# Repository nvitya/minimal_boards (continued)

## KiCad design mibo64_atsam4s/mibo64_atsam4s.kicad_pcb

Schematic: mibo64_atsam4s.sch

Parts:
C1: 10nF; C_0603_HandSoldering
C2, C3: 22pF; C_0603_HandSoldering
C4, C5, C7, C8, C9, C13, C14: 100nF; C_0603_HandSoldering
C6, C12: 10uF; C_0603_HandSoldering
C10, C11: 1uF; C_0603_HandSoldering
D1: YELLOW; LED_0603_HandSoldering
D2: GREEN; LED_0603_HandSoldering
J1: EXT1; Pin_Header_Straight_1x26_Pitch2.54mm
J2: SWD; Pin_Header_Straight_1x04_Pitch2.54mm
J3: EXT2; Pin_Header_Straight_1x26_Pitch2.54mm
J4: USB_OTG; USB_Micro-B
MK1, MK2: Mounting_Hole; MountingHole_3.2mm_M3
R1: 10k; R_0603_HandSoldering
R2, R3: 1k; R_0603_HandSoldering
R4, R5: 22R; R_0603_HandSoldering
SW1: RESET; SW_SPST_FSMSM
U1: ATSAM4SxB; LQFP-64_10x10mm_Pitch0.5mm
U2: LD1117S33CTR; SOT-223
Y1: 12MHz; Crystal_HC49-4H_Vertical

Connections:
+3V3: C4.1, C5.1, C7.1, C9.1, C10.1, C12.1, D1.2, D2.2, J1.2, J2.1, J3.25, R1.2, U1.1 (ADVREF), U1.7 (VDDIN), U1.18 (VDDIO), U1.45 (VDDIO), U1.58 (VDDIO), U2.2 (VO)
/1V2: C11.1, C13.1, C14.1, U1.8 (VDDOUT), U1.12 (VDDCORE), U1.24 (VDDCORE), U1.54 (VDDCORE), U1.64 (VDDPLL)
/5V: C6.1, C8.1, J1.25, J3.2, J4.1 (VBUS), U2.3 (VI)
/ERASE-PB12: J1.6, U1.55 (ERASE/PB12)
/PA0: J3.4, U1.48 (PA0)
/PA1: J3.5, R3.1, U1.47 (PA1)
/PA2: J3.6, U1.44 (PA2)
/PA3: J3.7, U1.43 (PA3)
/PA4: J3.12, U1.36 (PA4)
/PA5: J3.13, U1.35 (PA5)
/PA6: J3.14, U1.34 (PA6)
/PA7: J3.15, U1.32 (PA7)
/PA8: J3.16, U1.31 (PA8)
/PA9: J3.17, U1.30 (PA9)
/PA10: J3.18, U1.29 (PA10)
/PA11: J3.19, U1.28 (PA11)
/PA12: J3.20, U1.27 (PA12)
/PA13: J3.24, U1.22 (PA13)
/PA14: J1.22, U1.21 (PA14)
/PA15: J1.23, U1.20 (PA15)
/PA16: J1.24, U1.19 (PA16)
/PA17: J1.15, U1.9 (PA17)
/PA18: J1.16, U1.10 (PA18)
/PA19: J1.18, U1.13 (PA19)
/PA20: J1.21, U1.16 (PA20)
/PA21: J1.17, U1.11 (PA21)
/PA22: J1.19, U1.14 (PA22)
/PA23: J1.20, U1.15 (PA23)
/PA24: J3.23, U1.23 (PA24)
/PA25: J3.22, U1.25 (PA25)
/PA26: J3.21, U1.26 (PA26)
/PA27: J3.11, U1.37 (PA27)
/PA28: J3.10, U1.38 (PA28)
/PA29: J3.9, U1.41 (PA29)
/PA30: J3.8, U1.42 (PA30)
/PA31: J3.3, U1.52 (PA31)
/PB0: J1.11, U1.3 (PB0/AD4)
/PB1: J1.12, U1.4 (PB1/AD5)
/PB2: J1.13, U1.5 (PB2/AD6)
/PB3: J1.14, U1.6 (PB3/AD7)
/PB13: J1.9, U1.59 (PB13/DAC0)
/PB14: J1.10, U1.63 (PB14/DAC1)
/RESET: C1.1, J1.5, R1.1, SW1.2, U1.39 (~RESET)
/SWCLK-PB7: J2.3, U1.53 (TCK/SWCLK/PB7)
/SWDIO-PB6: J2.2, U1.51 (TMS/SWDIO/PB6)
/TDI-PB4: J1.3, U1.33 (TDI/PB4)
/TDO-PB5: J1.4, U1.49 (TDO/SWO/PB5)
/USBDM-PB10: J1.7, R5.1, U1.56 (USBDM/PB10)
/USBDP-PB11: J1.8, R4.1, U1.57 (USBDP/PB11)
/XIN: C3.1, U1.62 (XIN/PB9), Y1.1
/XOUT: C2.1, U1.61 (XOUT/PB8), Y1.2
unnamed: D1.1, R2.2
unnamed: D2.1, R3.2
unnamed: J4.2 (D-), R5.2
unnamed: J4.3 (D+), R4.2

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
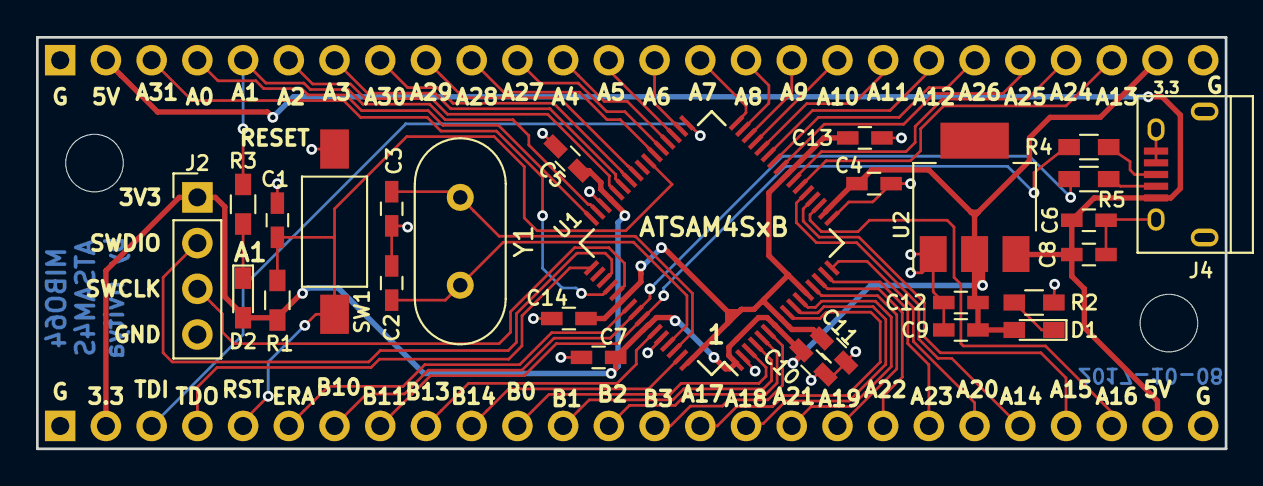
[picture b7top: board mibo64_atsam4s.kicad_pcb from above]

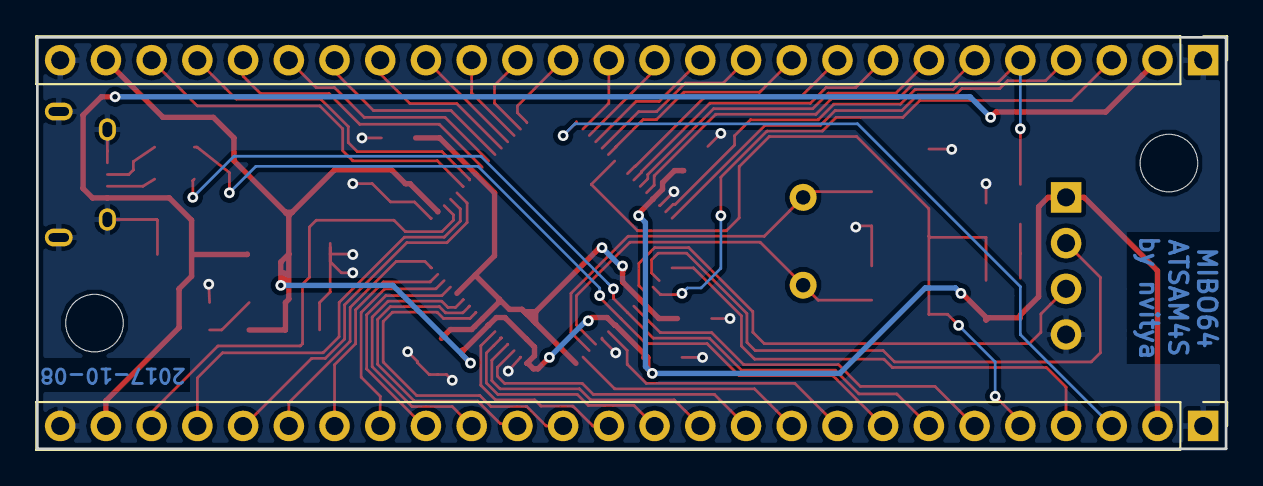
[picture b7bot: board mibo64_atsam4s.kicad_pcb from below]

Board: 2 copper layers, 66.0 x 22.9 mm, 31 parts (2 on the bottom side), 56 nets.

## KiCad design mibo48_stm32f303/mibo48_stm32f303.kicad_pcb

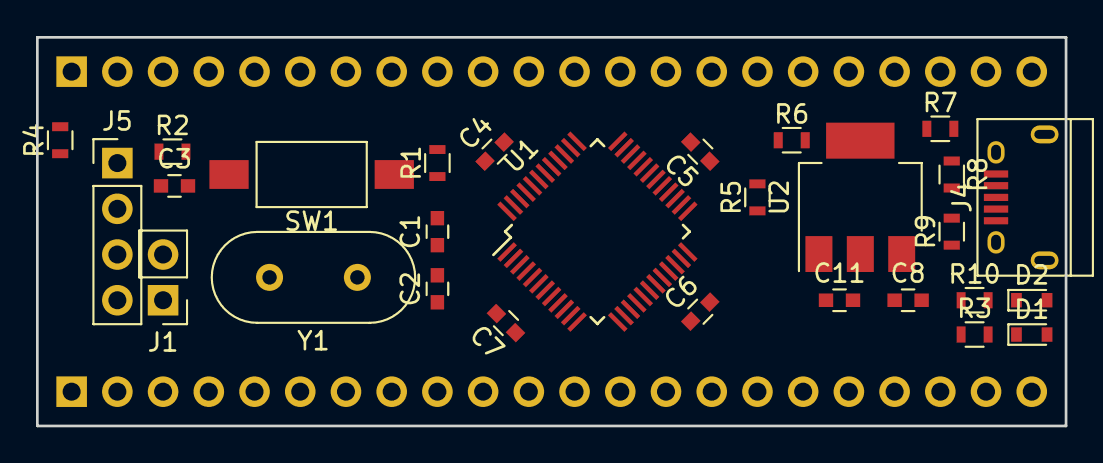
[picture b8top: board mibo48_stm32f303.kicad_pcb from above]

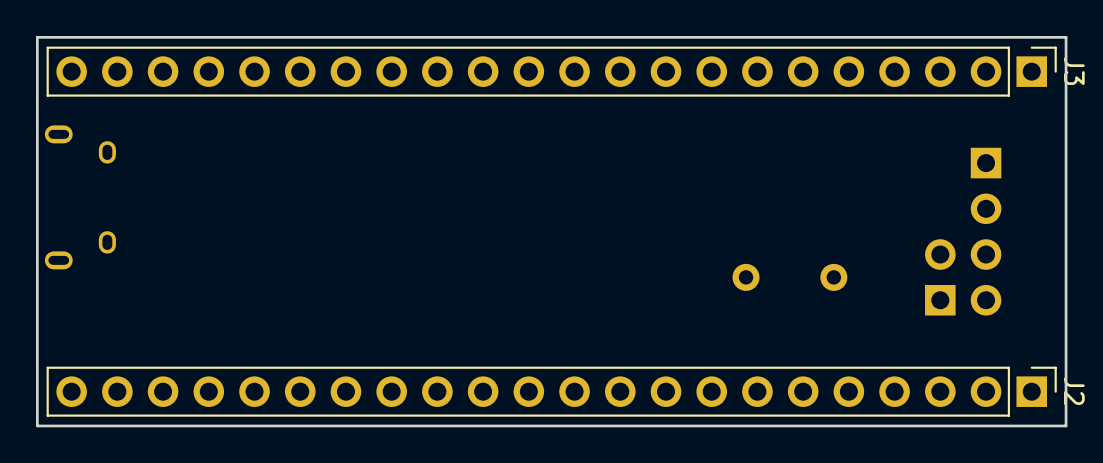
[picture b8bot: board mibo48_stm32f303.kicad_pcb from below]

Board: 2 copper layers, 57.1 x 21.6 mm, 30 parts (2 on the bottom side), 48 nets, no tracks yet.

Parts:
C1, C2: 22pF; C_0603
C3: 10nF; C_0603
C4, C5, C6, C7: 100nF; C_0603
C8, C11: 4.7uF; C_0603
D1, D2: GREEN; D_0603
J1: Conn_01x02; Pin_Header_Straight_1x02_Pitch2.54mm
J2, J3: Conn_01x22; Pin_Header_Straight_1x22_Pitch2.54mm
J4: USB_B_Micro; USB_Micro-B
J5: Conn_01x04; Pin_Header_Straight_1x04_Pitch2.54mm
R1: 100k; R_0603
R2: 10k; R_0603
R3, R10: 1k; R_0603
R4, R5, R6: 0R; R_0603
R7: 1.5k; R_0603
R8, R9: 22R; R_0603
SW1: Reset; SW_SPST_FSMSM
U1: STM32F303CBTx; LQFP-48_7x7mm_Pitch0.5mm
U2: AMS1117-3.3; SOT-223
Y1: 8MHz; Crystal_HC49-U_Vertical

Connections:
+3V3: C4.1, C5.1, C6.1, C7.1, C11.1, J1.2, J2.2, J3.21, J5.1, R2.2, R3.2, R4.2, R10.2, U1.9, U1.24, U1.36, U1.48, U2.2
/5V: C8.1, J2.21, J3.2, J4.1, R6.1, U2.3
/BOOT0: J1.1, J2.3, R1.1, U1.44
/LED1: D1.1, J3.18, U1.2
/OSC32_IN: J3.19, U1.3
/OSC32_OUT: J3.20, U1.4
/OSC_IN: C1.1, U1.5, Y1.1
/OSC_OUT: C2.1, U1.6, Y1.2
/PA0: J3.4, U1.10
/PA1: J3.5, U1.11
/PA2: J3.6, U1.12
/PA3: J3.7, U1.13
/PA4: J3.8, U1.14
/PA5: J3.9, U1.15
/PA6: J3.10, U1.16
/PA7: J3.11, U1.17
/PA8: J3.12, U1.29
/PA9: J3.13, U1.30
/PA10: J3.14, U1.31
/PA11: J3.15, R9.1, U1.32
/PA12: J3.16, R8.1, U1.33
/PA15: J3.17, R5.2, U1.38
/PB0: J2.5, U1.18
/PB1: J2.6, U1.19
/PB2: J2.7, U1.20
/PB3: J2.8, U1.39
/PB4: J2.9, U1.40
/PB5: J2.10, U1.41
/PB6: J2.11, U1.42
/PB7: J2.12, U1.43
/PB8: J2.13, U1.45
/PB9: J2.14, U1.46
/PB10: J2.15, U1.21
/PB11: J2.16, U1.22
/PB12: J2.17, U1.25
/PB13: J2.18, U1.26
/PB14: J2.19, U1.27
/PB15: J2.20, U1.28
/RESET: C3.1, J2.4, R2.1, SW1.1, U1.7
/SWDCLK: J5.3, U1.37
/SWDIO: J5.2, U1.34
/VBAT: J3.3, R4.1, U1.1
GND: C1.2, C2.2, C3.2, C4.2, C5.2, C6.2, C7.2, C8.2, C11.2, D2.1, J2.1, J2.22, J3.1, J3.22, J4.5, J4.6, J5.4, R1.2, SW1.2, U1.8, U1.23, U1.35, U1.47, U2.1
unnamed: D1.2, R3.1
unnamed: D2.2, R10.1
unnamed: J4.2, R9.2
unnamed: J4.3, R7.1, R8.2
unnamed: R5.1, R6.2, R7.2

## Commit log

2018-09-13 STM32F303Cx plan added, not ready yet
2018-09-15 - fully routed, only labelling is missing - kicad 5 project with new libraries and footprints
2018-09-15 project directory rename
2018-09-15 project renamed from STM32F303 to STM32
2018-09-15 draft of the 64 pin variant
2018-09-16 almost fully routed
2018-09-16 small layout change
2018-09-16 fully routed, labelling still missing
2018-09-16 imxrt1020 project added, MCU schematic symbol done
2018-09-16 Old ATSAM4S project added
2018-09-16 readme file added
2018-09-17 mibo20 stm32 project created
2018-09-22 Test commit
2018-09-23 V1.0 - Fully routed with description
2018-09-23 MIBO20-STM32 added
2018-09-23 small trace tweak
2018-09-23 added version to pcb
2018-09-23 MIBO48 Labelling finished
2018-09-23 MIBO64-STM32 finished.
2018-09-23 SWD connector rotated
2018-09-29 Q1 and SW1 swapped
2018-09-30 Jumper for USB added
2018-10-14 some progress with the imxrt
2018-10-20 routing finished
2018-10-21 captioning finished as well
2018-10-21 gerber files generated
2018-10-21 gerber files added
2018-10-21 gerber settings
2018-10-22 POR_B and double capacitors
2018-10-22 board measurements added
2018-11-16 board status update
2018-11-18 Pictures added
2018-11-21 version 2 created
2019-03-27 mibo48-xmc4 routing finished
2019-03-27 xmc4200 added
2019-03-28 captioned, gerbers
2020-02-28 mibo48-stm32g4
2020-03-07 MIBO64-ATSAME5X
2020-03-07 readme update
2021-11-10 Update README.md
    https://forum.kicad.info/t/warning-avoid-all-links-to-kicad-pcb-org-use-kicad-org/31521
2021-11-15 picture added
2021-11-15 photo added
